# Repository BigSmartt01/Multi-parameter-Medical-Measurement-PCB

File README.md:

# Multi-Parameter Patient Monitoring System

**Project Topic:** Design and Development of a Multi-Parameter Patient Monitoring System with ECG Arrhythmia Detection, Real-Time Data Storage, and Wireless Remote Display.

This repository holds the hardware design (schematic, PCB, footprints, fabrication files) for the patient-side sensor and actuator unit. Firmware and the ML/logic layer on the Raspberry Pi are maintained separately by the software team; this repo covers circuitry only.

## What this device does

The board sits at the patient's bedside and handles all direct sensor and actuator interfacing:

* Reads ECG (AD8232), SpO2/pulse (MAX30102), body temperature (DS18B20), and blood pressure cuff pressure (MPXHZ6400).
* Drives a pump and a solenoid/valve for the blood pressure cuff inflate/deflate cycle.
* Displays local status on a 2.4" OLED and gives audible alerts through a buzzer.
* Streams sensor data wirelessly and receives commands over WiFi/MQTT.

The Raspberry Pi 5 sits on the nurse side, runs the ML model (arrhythmia detection), logic, data storage, and drives an HDMI display plus a web app. It never touches the patient directly, all sensor/actuator interfacing is the ESP32's job.

## System architecture (high level)

```
\[Patient side]                              \[Nurse side]
ESP32 (sensors + actuators + OLED + buzzer)  <--MQTT/WiFi-->  Raspberry Pi 5 (ML, logic, storage, HDMI, web app)
```

MQTT topic structure (for reference, implemented in firmware):

Pi publishes (commands to ESP32):

* `pi/control/pump`
* `pi/control/valve`
* `pi/display/oled`
* `pi/control/buzzer`

Pi subscribes (data from ESP32):

* `esp32/sensors/ecg`
* `esp32/sensors/bp`
* `esp32/sensors/temp`
* `esp32/sensors/pulse`
* `esp32/status/pump`

A full block diagram will be added to `docs/` covering both the electrical and system-level data flow.

## Repository structure

```
Multi-parameter Medical Measurement/
|-- libraries/
|     |-- 3d          (3D models for footprints, if used)
|     |-- footprints   (custom KiCad footprints, e.g. module outlines)
|     |-- symbols      (custom KiCad symbols for breakout modules)
|-- fabrication         (gerbers, drill files, BOM, pick-and-place, for JLCPCB)
|-- kicad                (project file, schematic, PCB layout)
|-- docs                 (this documentation, block diagrams, reference notes)
```

## Hardware summary

|Subsystem|Part|Notes|
|-|-|-|
|MCU|ESP32 DevKit V1 (30 GPIO)|Mounted on female header for clearance|
|ECG|AD8232 breakout|LO+/LO- leads-off detection wired in|
|SpO2 / Pulse|MAX30102 breakout|I2C|
|Temperature|DS18B20|1-Wire, 4.7k pull-up|
|Blood pressure|MPXHZ6400AC6T1|SOIC-8, resistor divider scales output for ESP32 ADC|
|Display|2.4" OLED, SPI, 7-pin|CS tied to GND (only SPI device on board)|
|Alert|Piezo buzzer|Driven through BC337 NPN transistor stage|
|Pump|12V, MOSFET-switched|IRLB8721, flyback diode, gate pull-down|
|Solenoid/Valve|12V, MOSFET-switched|IRLB8721, flyback diode, gate pull-down|
|Power|3x 18650 (3S) + BMS|12.6V nominal, LM2596 module steps down to 5V|

Full pin mapping and design rationale are in [`docs/circuit\_documentation.md`](docs/circuit_documentation.md).

<p align="center">
  <br>
  <em>Fabricated single-layer patient-side monitoring board</em>
</p>

## Power architecture

<p align="center">
  <em>3x 18650 (3S) + BMS -> LM2596 buck -> 5V rail</em>
</p>

## Getting started

1. Open `kicad/Multi-parameter Medicals.kicad\_pro` in KiCad 9.0.7 or later.
2. Custom symbols and footprints for breakout modules (AD8232, MAX30102, LM2596 module, BMS module) live under `libraries/`, make sure these are added to your project's library table before opening the schematic, or KiCad will show missing symbol/footprint errors.
3. The board is single-layer, routed with net ties and jumper wires (JP1-JP6, NT1-NT3) to work around single-layer constraints. If you're re-routing, keep the ground pour intact between the analog sensor section (left side) and the motor/switching section (right side), see the documentation for why.
4. Before sending to fab, run a full DRC pass and verify trace widths on the high-current nets (battery/BMS input, pump, solenoid) against actual component current ratings.

## Team

Circuit design (schematic + PCB): Smart Ayodele
Firmware and ML/logic: student team

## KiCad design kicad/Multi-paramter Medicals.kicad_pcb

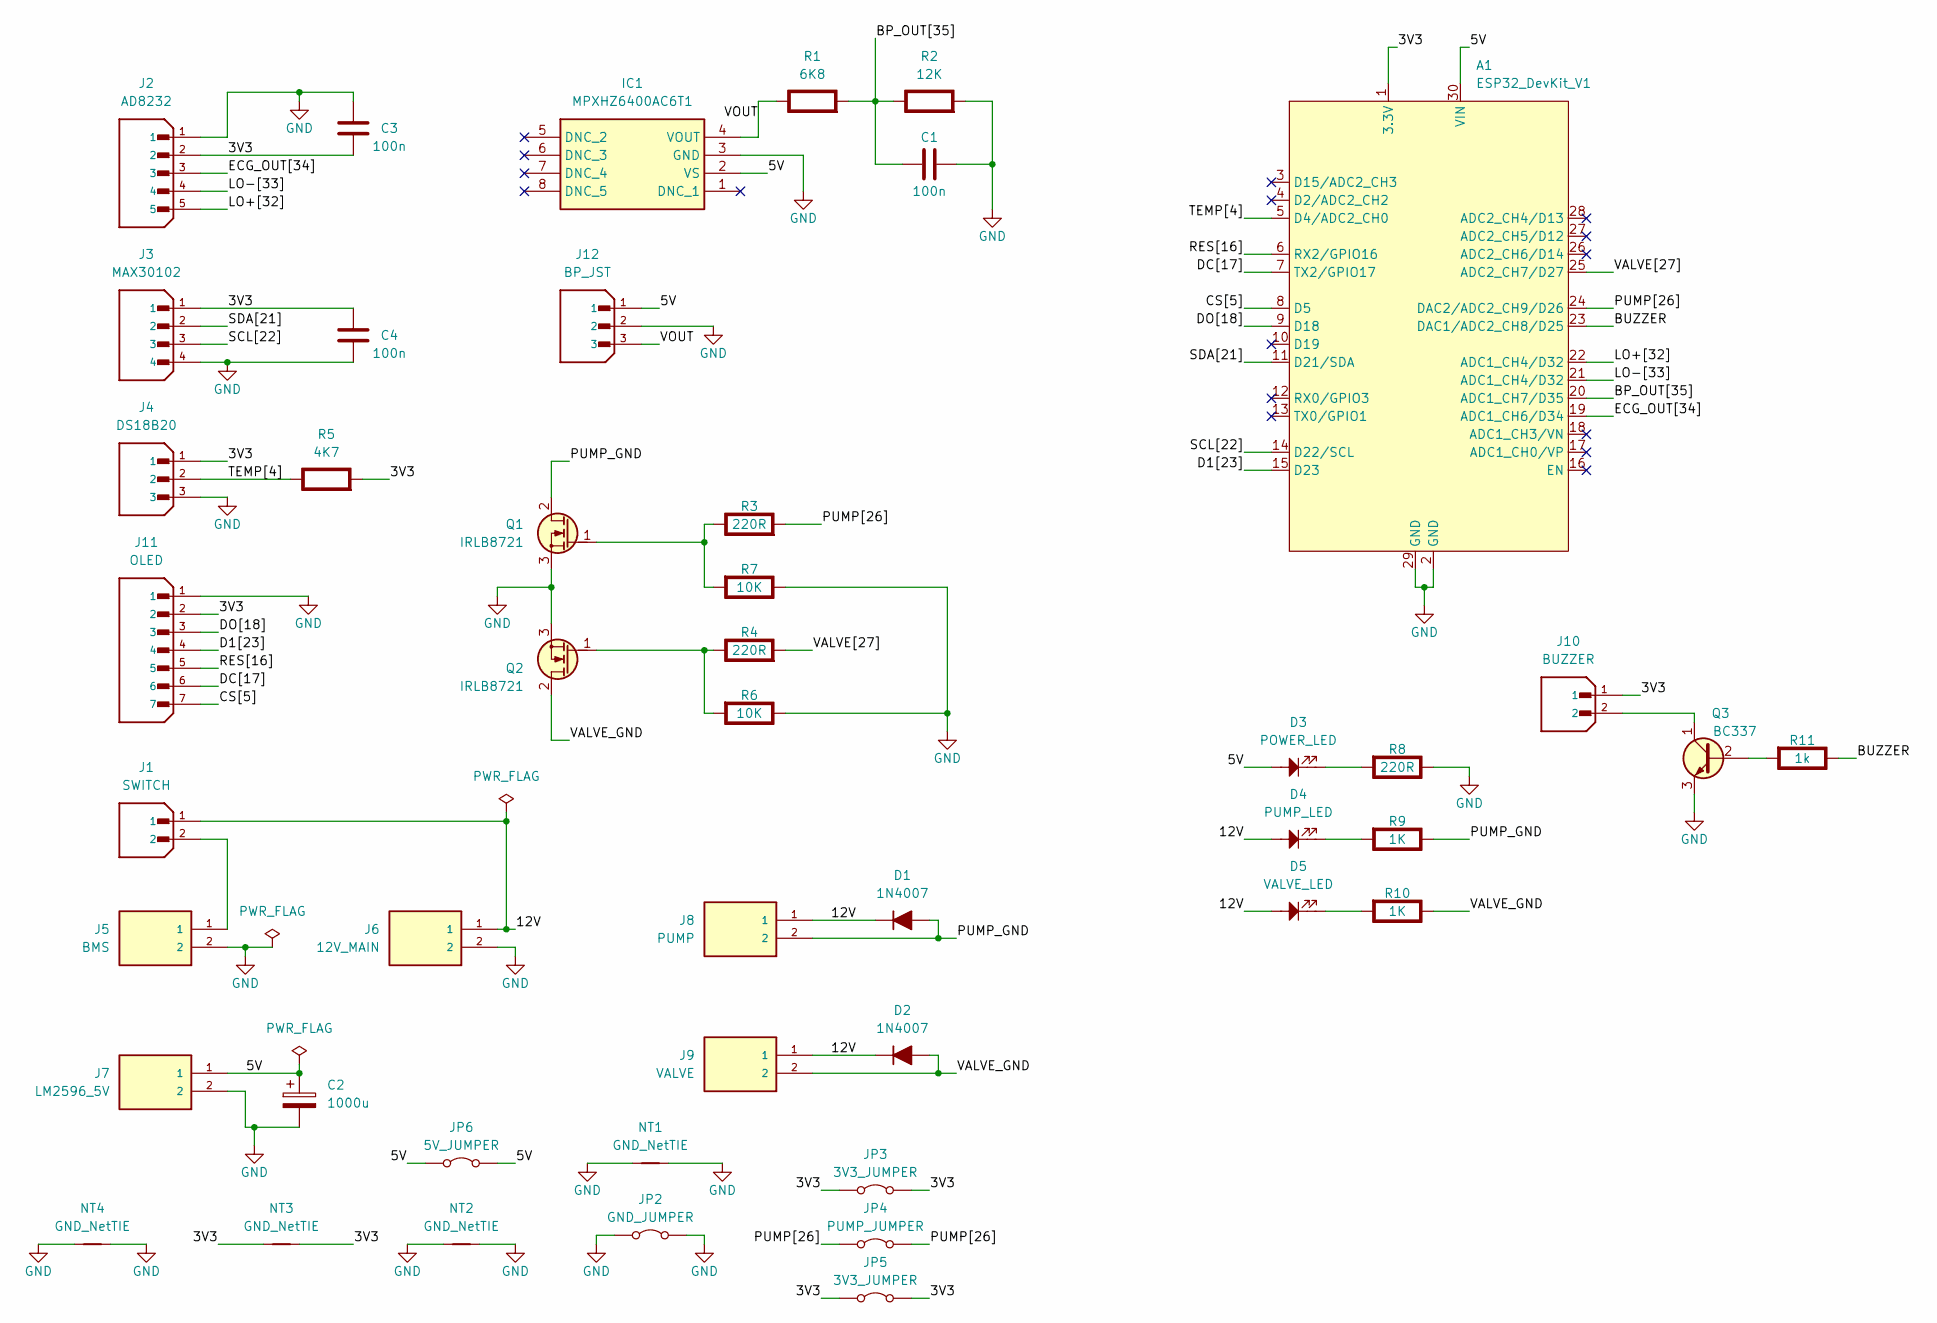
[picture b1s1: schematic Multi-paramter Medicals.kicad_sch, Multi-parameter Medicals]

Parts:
A1: ESP32_DevKit_V1; DOIT_ESP32_DEVKIT_30Pins
C1, C3, C4: 100n; C_Disc_D5.0mm_W2.5mm_P5.00mm
C2: 1000u; CP_Radial_D10.0mm_P7.50mm
D1, D2: 1N4007; D_DO-41_SOD81_P10.16mm_Horizontal
D3: POWER_LED; LED_D5.0mm
D4: PUMP_LED; LED_D5.0mm
D5: VALVE_LED; LED_D5.0mm
IC1: MPXHZ6400AC6T1; Manufacturer_Part_Number MPXHZ6400AC6T1; Mouser Part Number 841-MPXHZ6400AC6T1
J1: SWITCH; JST_B2B-XH-A; PARTREV N/A
J2: AD8232; JST_B5B-XH-A; PARTREV 7/4/21
J3: MAX30102; JST_B4B-XH-A; PARTREV 7/4/21
J4: DS18B20; JST_B3B-XH-A; PARTREV 7/4/21
J5: BMS; TB002-500-02BE
J6: 12V_MAIN; TB002-500-02BE
J7: LM2596_5V; TB002-500-02BE
J8: PUMP; TB002-500-02BE
J9: VALVE; TB002-500-02BE
J10: BUZZER; JST_B2B-XH-A; PARTREV N/A
J11: OLED; JST_B7B-XH-A; PARTREV 7/4/21
J12: BP_JST; JST_B3B-XH-A; PARTREV 7/4/21
JP2: GND_JUMPER; Jumper_P12.70mm_D0.7mm
JP3, JP5: 3V3_JUMPER; Jumper_P15.24mm_D0.7mm
JP4: PUMP_JUMPER; Jumper_P15.24mm_D0.7mm
JP6: 5V_JUMPER; Jumper_P20.32mm_D0.7mm
NT1, NT2, NT3, NT4: GND_NetTIE; Jumper_P7.62mm_D0.7mm
Q1, Q2: IRLB8721; TO-220-3_Vertical
Q3: BC337; TO-92_Inline_Wide
R1: 6K8; R_Axial_DIN0309_L9.0mm_D3.2mm_P12.70mm_Horizontal; Rating W
R2: 12K; R_Axial_DIN0309_L9.0mm_D3.2mm_P12.70mm_Horizontal; Rating W
R3, R4, R8: 220R; R_Axial_DIN0309_L9.0mm_D3.2mm_P12.70mm_Horizontal; Rating W
R5: 4K7; R_Axial_DIN0309_L9.0mm_D3.2mm_P12.70mm_Horizontal; Rating W
R6, R7: 10K; R_Axial_DIN0309_L9.0mm_D3.2mm_P12.70mm_Horizontal; Rating W
R9, R10: 1K; R_Axial_DIN0309_L9.0mm_D3.2mm_P12.70mm_Horizontal; Rating W
R11: 1k; R_Axial_DIN0309_L9.0mm_D3.2mm_P12.70mm_Horizontal; Rating W

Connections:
/3V3: A1.1 (3.3V), C3.2, C4.1, J2.2, J3.1, J4.1, J10.1, J11.2, JP3.1 (A), JP3.2 (B), JP5.1 (A), JP5.2 (B), NT3.1, NT3.2, R5.2 (-)
/5V: A1.30 (VIN), C2.1, D3.2, IC1.2 (VS), J7.1, J12.1, JP6.1 (A), JP6.2 (B)
/12V: D1.1 (K), D2.1 (K), D4.2, D5.2, J1.1, J6.1, J8.1, J9.1
/BP_OUT[35]: A1.20 (ADC1_CH7/D35), C1.2, R1.2 (-), R2.1 (+)
/BUZZER: A1.23 (DAC1/ADC2_CH8/D25), R11.1 (+)
/CS[5]: A1.8 (D5), J11.7
/D1[23]: A1.15 (D23), J11.4
/DC[17]: A1.7 (TX2/GPIO17), J11.6
/DO[18]: A1.9 (D18), J11.3
/ECG_OUT[34]: A1.19 (ADC1_CH6/D34), J2.3
/LO+[32]: A1.22 (ADC1_CH4/D32), J2.5
/LO-[33]: A1.21 (ADC1_CH4/D32), J2.4
/PUMP[26]: A1.24 (DAC2/ADC2_CH9/D26), JP4.1 (A), JP4.2 (B), R3.2 (-)
/PUMP_GND: D1.2 (A), J8.2, Q1.2 (D), R9.1 (+)
/RES[16]: A1.6 (RX2/GPIO16), J11.5
/SCL[22]: A1.14 (D22/SCL), J3.3
/SDA[21]: A1.11 (D21/SDA), J3.2
/TEMP[4]: A1.5 (D4/ADC2_CH0), J4.2, R5.1 (+)
/VALVE[27]: A1.25 (ADC2_CH7/D27), R4.2 (-)
/VALVE_GND: D2.2 (A), J9.2, Q2.2 (D), R10.1 (+)
/VOUT: IC1.4 (VOUT), J12.3, R1.1 (+)
GND: A1.2 (GND), A1.29 (GND), C1.1, C2.2, C3.1, C4.2, IC1.3 (GND), J2.1, J3.4, J4.3, J5.2, J6.2, J7.2, J11.1, J12.2, JP2.1 (A), JP2.2 (B), NT1.1, NT1.2, NT2.1, NT2.2, NT4.1, NT4.2, Q1.3 (S), Q2.3 (S), Q3.3 (E), R2.2 (-), R6.1 (+), R7.1 (+), R8.1 (+)
unnamed: J1.2, J5.1
unnamed: Q1.1 (G), R3.1 (+), R7.2 (-)
unnamed: Q2.1 (G), R4.1 (+), R6.2 (-)
unnamed: Q3.2 (B), R11.2 (-)
unnamed: J10.2, Q3.1 (C)
unnamed: D3.1, R8.2 (-)
unnamed: D4.1, R9.2 (-)
unnamed: D5.1, R10.2 (-)

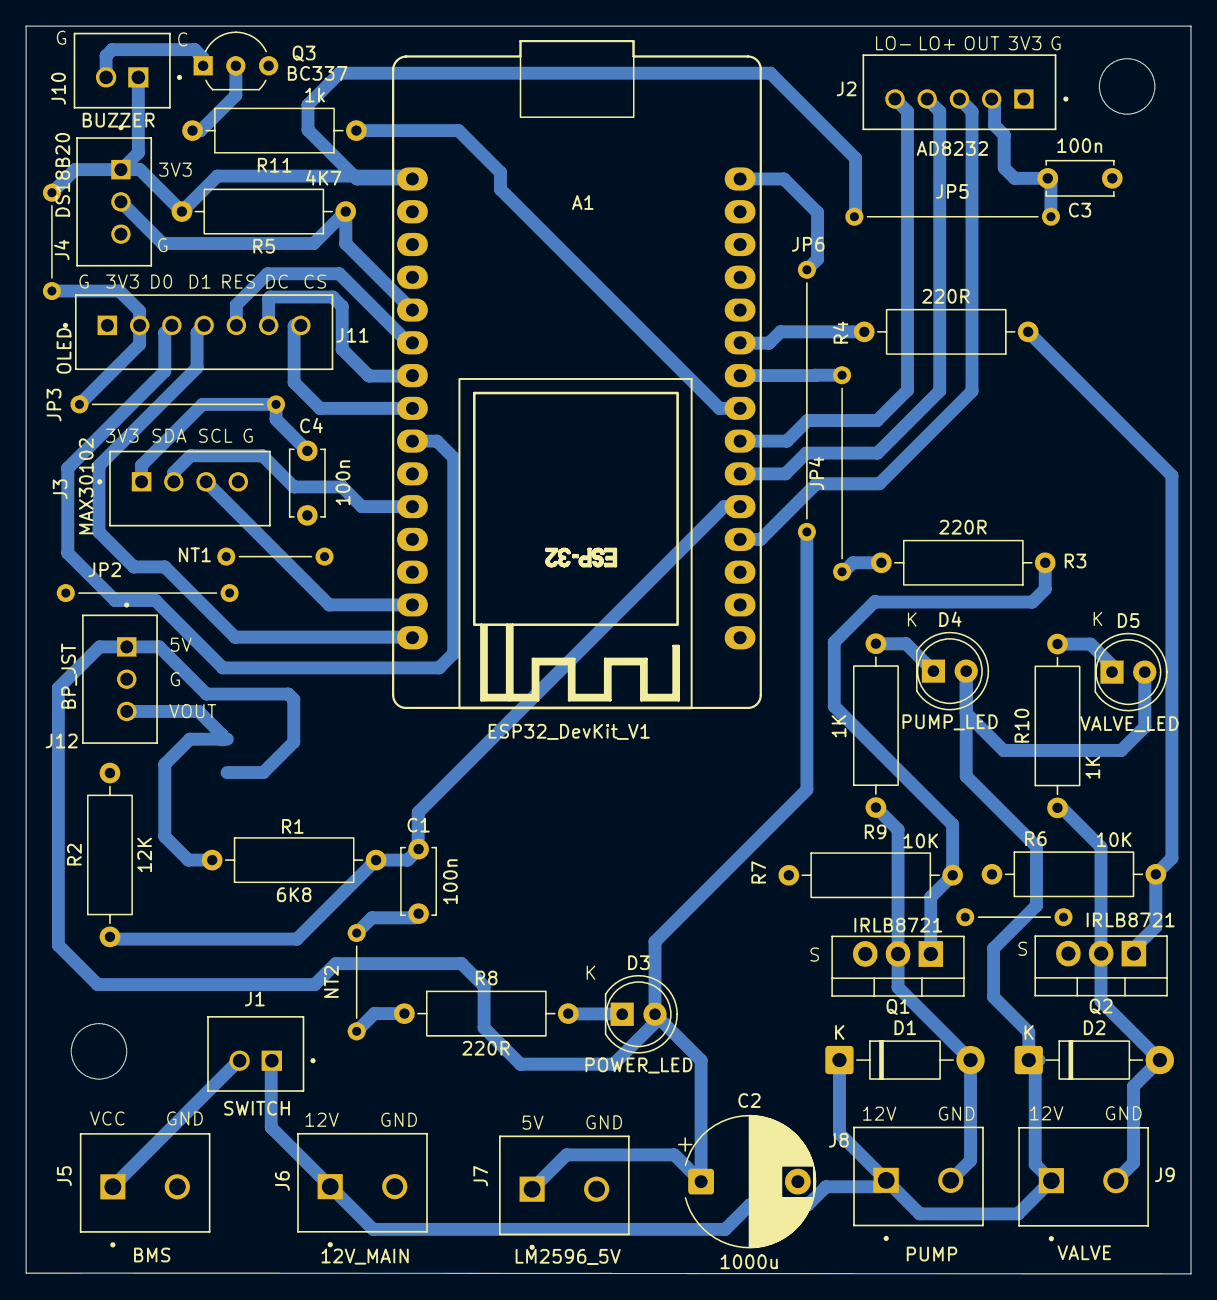
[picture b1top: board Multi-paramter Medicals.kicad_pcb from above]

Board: 2 copper layers, 90.3 x 96.7 mm, 46 parts (1 on the bottom side), 30 nets.
